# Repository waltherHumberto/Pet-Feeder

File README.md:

Este é o README para o projeto IOT de um dispensador de comida para pet, que utiliza o microcontrolador ESP32 e um servo motor para automatizar a alimentação de animais de estimação. O projeto também inclui uma configuração de aplicativo APK para controle remoto do dispensador.

Funcionalidades

    Dispensação automática de comida para animais de estimação em horários programados.
    Controle remoto do dispensador por meio de um aplicativo móvel.
    Configuração flexível de horários e quantidade de alimentação.
    Interface de usuário intuitiva para fácil operação.

Componentes do Projeto

    ESP32: Microcontrolador responsável pelo controle do dispensador e comunicação com o aplicativo móvel.
    Servo Motor: Atua como o mecanismo de dispensação da comida.
    Sensor de Alimentação: Opcionalmente, um sensor pode ser utilizado para detectar quando o recipiente de comida está vazio e enviar notificações para o aplicativo.
    Fonte de Alimentação: Fornecer energia para o ESP32, servo motor e outros componentes necessários.
    Aplicativo APK: Um aplicativo móvel que permite ao usuário controlar o dispensador remotamente, programar horários e monitorar o status de alimentação.

Instalação e Configuração

    Clone ou faça o download deste repositório para o seu computador.
    Certifique-se de ter o ambiente de desenvolvimento necessário para programar o ESP32.
    Conecte o ESP32 ao seu computador e faça o upload do código fornecido para o microcontrolador.
    Monte o servo motor no dispensador de comida, garantindo que esteja corretamente conectado ao ESP32.
    Conecte os fios do sensor de alimentação, se estiver sendo utilizado, ao ESP32.
    Conecte a fonte de alimentação ao ESP32.
    Siga as instruções fornecidas no aplicativo APK para instalá-lo em seu dispositivo móvel.
    Abra o aplicativo, siga o processo de configuração inicial para conectar o aplicativo ao ESP32.
    Configure os horários de alimentação e a quantidade de comida desejada por meio do aplicativo.

Uso

    Após configurar o dispensador e o aplicativo móvel, você pode programar horários de alimentação para o seu pet.
    O dispenser irá ativar o servo motor nos horários programados para dispensar a quantidade de comida definida.
    Você também pode usar o aplicativo para alimentar manualmente o seu pet a qualquer momento.
    O sensor de alimentação (se utilizado) irá monitorar o nível de comida no recipiente e notificará o aplicativo quando estiver vazio.

Contribuição

Contribuições são bem-vindas! Se você tiver sugestões, correções de bugs ou melhorias para este projeto, fique à vontade para enviar um pull request ou abrir uma issue neste repositório.

Licença
De Uso público

Se você tiver alguma dúvida ou precisar entrar em contato, sinta-se à vontade para enviar um e-mail para [waltherhumberto@gmail.com].

Agradecemos a todos os contribuidores e recursos de código aberto utilizados neste projeto.

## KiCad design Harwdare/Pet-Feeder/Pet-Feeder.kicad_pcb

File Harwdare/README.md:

Hardware do Dispensador de Comida para Pet

Este é o README para o hardware do projeto de Dispensador de Comida para Pet. O hardware consiste nos componentes físicos necessários para a construção e funcionamento do dispensador, incluindo o microcontrolador ESP32, o servo motor e outros elementos relevantes.
Componentes

    ESP32: Microcontrolador responsável pelo controle do dispensador e comunicação com o aplicativo móvel.
    Servo Motor: Mecanismo de dispensação da comida, utilizado para movimentar o compartimento de armazenamento.
    Sensor de Nível de Comida (opcional): Sensor utilizado para detectar o nível de comida no recipiente e enviar notificações para o aplicativo.
    Fonte de Alimentação: Fornecer energia para o ESP32, servo motor e outros componentes necessários.
    Recipiente de Comida: Compartimento onde a comida para pet é armazenada.
    Botões ou Interface de Controle: Componentes utilizados para a interação com o dispensador, como programação manual e ajuste de configurações.

Montagem

    Conecte o servo motor ao ESP32 seguindo as especificações do fabricante e as instruções do firmware.
    Conecte o sensor de nível de comida (se utilizado) ao ESP32, de acordo com as instruções da biblioteca correspondente.
    Certifique-se de que o ESP32 esteja devidamente alimentado com a fonte de alimentação adequada.
    Monte o recipiente de comida no local designado, garantindo que esteja bem fixado.
    Verifique a correta conexão e posicionamento dos botões ou da interface de controle para facilitar a interação com o dispensador.

Configuração Adicional

    Caso seja necessário, conecte o dispensador à rede Wi-Fi para permitir a comunicação com o aplicativo móvel.
    Certifique-se de configurar corretamente o firmware para que o hardware e o aplicativo móvel estejam sincronizados.

Uso

    Após a montagem e configuração do hardware, alimente o dispensador com energia.
    O microcontrolador ESP32 irá inicializar e aguardar os comandos do aplicativo móvel ou dos botões de controle.
    Utilize o aplicativo móvel para programar horários de alimentação, configurar a quantidade de comida e outras preferências.
    Quando o horário de alimentação programado for alcançado, o microcontrolador acionará o servo motor para dispensar a quantidade de comida definida.
    Caso seja utilizado um sensor de nível de comida, ele irá monitorar o recipiente e enviar notificações quando estiver vazio.
    O usuário também pode utilizar os botões ou a interface de controle para programar manualmente a alimentação ou ajustar as configurações.

Contribuição

Contribuições são bem-vindas! Se você tiver sugestões, correções ou melhorias relacionadas ao hardware do dispensador de comida para pet, fique à vontade para enviar um pull request ou abrir uma issue neste repositório.

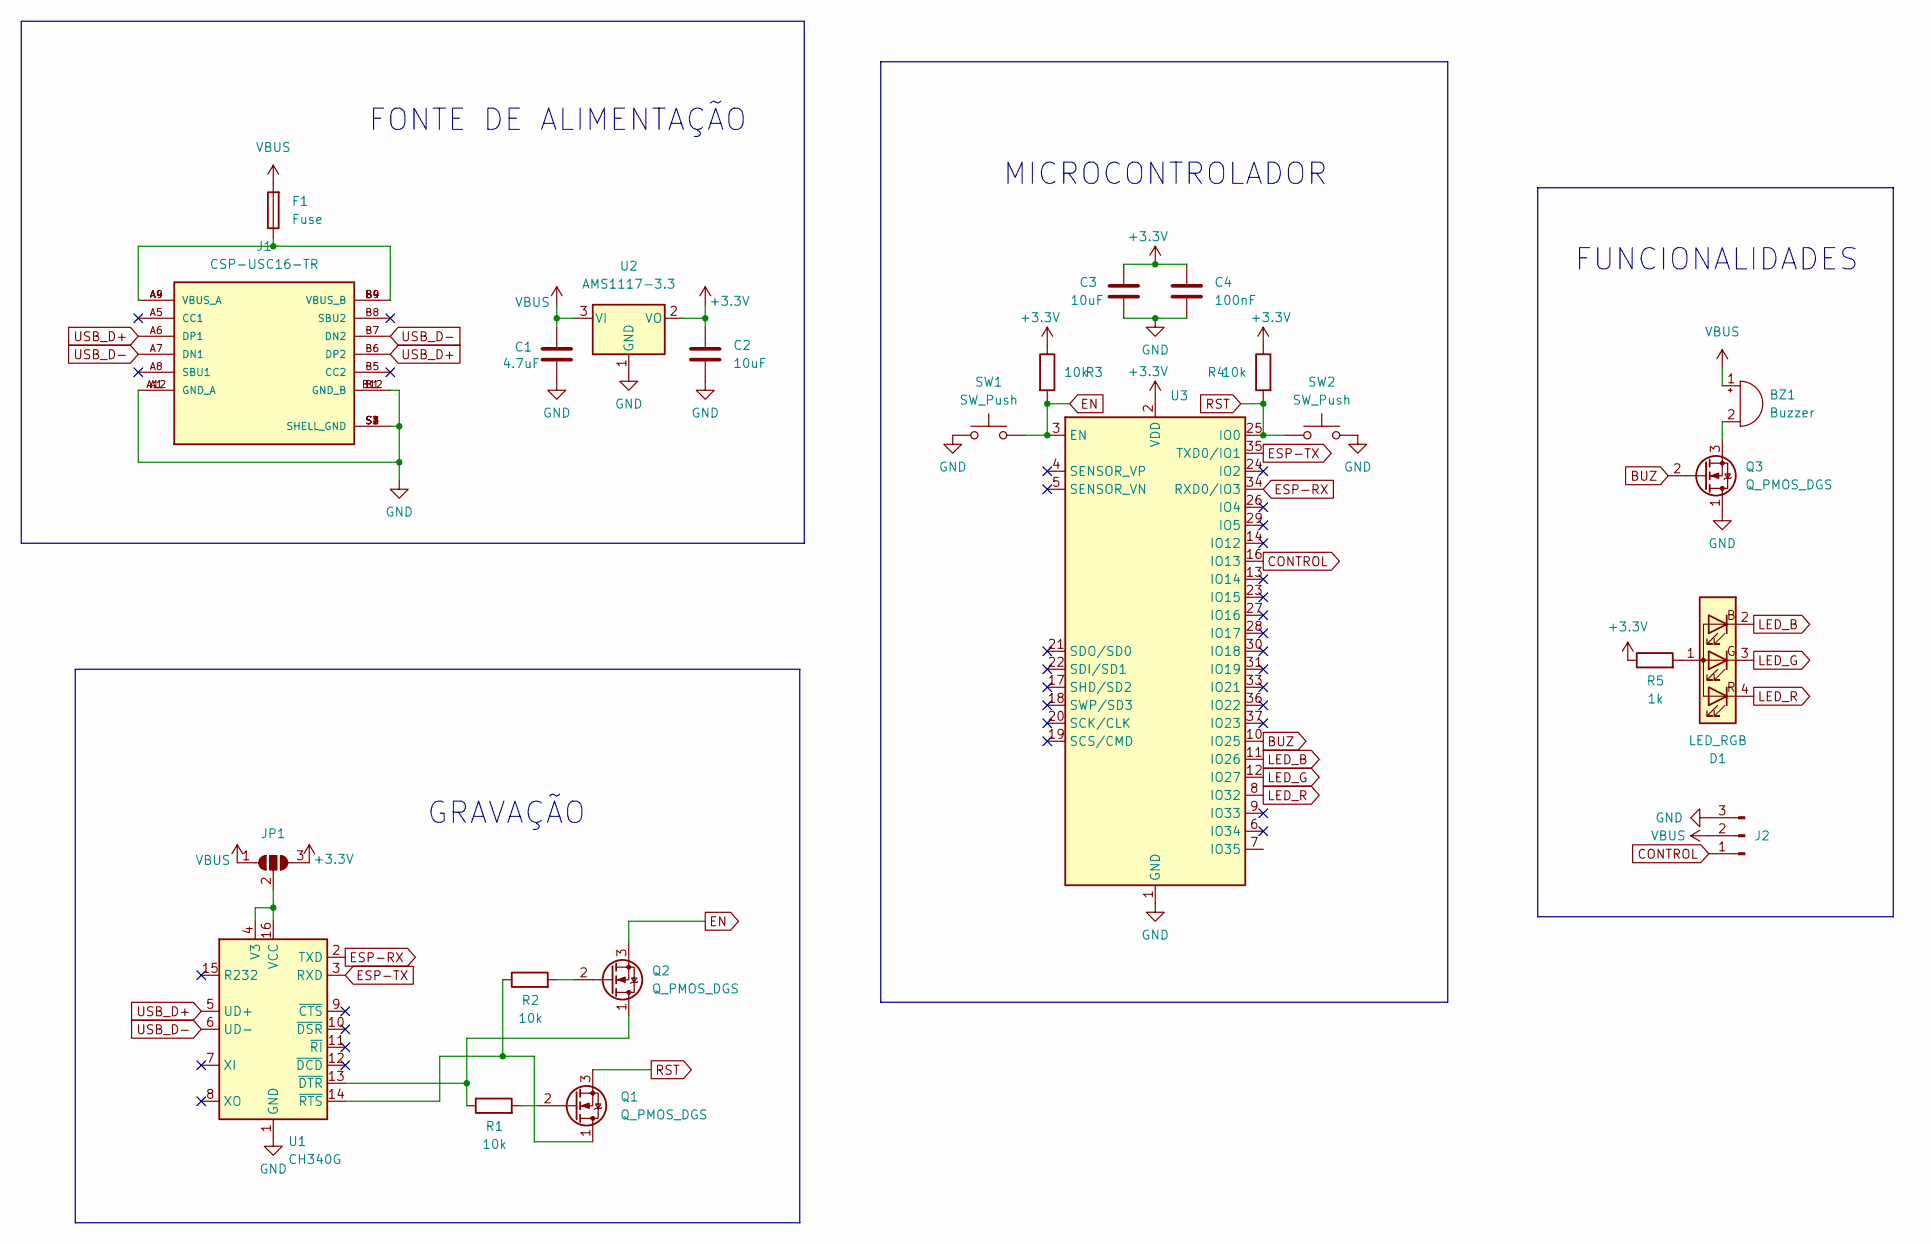
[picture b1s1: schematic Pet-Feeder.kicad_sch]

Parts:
BZ1: Buzzer; Buzzer_12x9.5RM7.6
C1: 4.7uF; C_1206_3216Metric
C2: 10uF; C_1206_3216Metric
C3: 10uF; C_0201_0603Metric
C4: 100nF; C_1206_3216Metric
D1: LED_RGB; LED_Avago_PLCC4_3.2x2.8mm_CW
F1: Fuse; R_1206_3216Metric
J1: CSP-USC16-TR; USB_C_Receptacle_Palconn_UTC16-G; PARTREV A0
J2: Conn_01x03_Male; PinSocket_1x03_P2.54mm_Vertical
JP1: SolderJumper_3_Open; SolderJumper-3_P1.3mm_Open_RoundedPad1.0x1.5mm
Q1, Q2, Q3: Q_PMOS_DGS; SOT-23-3
R1, R2, R3, R4: 10k; R_0201_0603Metric
R5: 1k; R_0201_0603Metric
SW1, SW2: SW_Push; SW_Push_1P1T_NO_CK_KSC6xxJ
U1: CH340G; SOIC-16_3.9x9.9mm_P1.27mm
U2: AMS1117-3.3; SOT-223-3_TabPin2
U3: ESP32-WROOM-32D; ESP32-WROOM-32

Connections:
+3.3V: C2.1, C3.1, C4.1, JP1.3 (B), R3.1, R4.1, R5.1, U2.2 (VO), U3.2 (VDD)
BUZ: Q3.2 (G), U3.10 (IO25)
CONTROL: J2.1, U3.16 (IO13)
EN: Q2.3 (S), R3.2, SW1.2, U3.3 (EN)
ESP-RX: U1.2 (TXD), U3.34 (RXD0/IO3)
ESP-TX: U1.3 (RXD), U3.35 (TXD0/IO1)
GND: C1.2, C2.2, C3.2, C4.2, J1.A1 (GND_A), J1.A12 (GND_A), J1.B1 (GND_B), J1.B12 (GND_B), J1.S1 (SHELL_GND), J1.S2 (SHELL_GND), J1.S3 (SHELL_GND), J1.S4 (SHELL_GND), J2.3, Q3.1 (D), SW1.1, SW2.1, U1.1 (GND), U2.1 (GND), U3.1 (GND), U3.15 (GND), U3.38 (GND), U3.39 (GND)
LED_B: D1.2 (BK), U3.11 (IO26)
LED_G: D1.3 (GK), U3.12 (IO27)
LED_R: D1.4 (RK), U3.8 (IO32)
unnamed: BZ1.2 (+), Q3.3 (S)
unnamed: D1.1 (A), R5.2
unnamed: F1.1, J1.A4 (VBUS_A), J1.A9 (VBUS_A), J1.B4 (VBUS_B), J1.B9 (VBUS_B)
unnamed: JP1.2 (C), U1.4 (V3), U1.16 (VCC)
unnamed: Q2.1 (D), R1.1, U1.13 (~DTR)
unnamed: Q1.2 (G), R1.2
unnamed: Q2.2 (G), R2.2
unnamed: Q1.1 (D), R2.1, U1.14 (~RTS)
RST: Q1.3 (S), R4.2, SW2.2, U3.25 (IO0)
USB_D+: J1.A6 (DP1), J1.B6 (DP2), U1.5 (UD+)
USB_D-: J1.A7 (DN1), J1.B7 (DN2), U1.6 (UD-)
VBUS: BZ1.1 (-), C1.1, F1.2, J2.2, JP1.1 (A), U2.3 (VI)

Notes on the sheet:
FONTE DE ALIMENTAÇÃO
MICROCONTROLADOR
GRAVAÇÃO
FUNCIONALIDADES

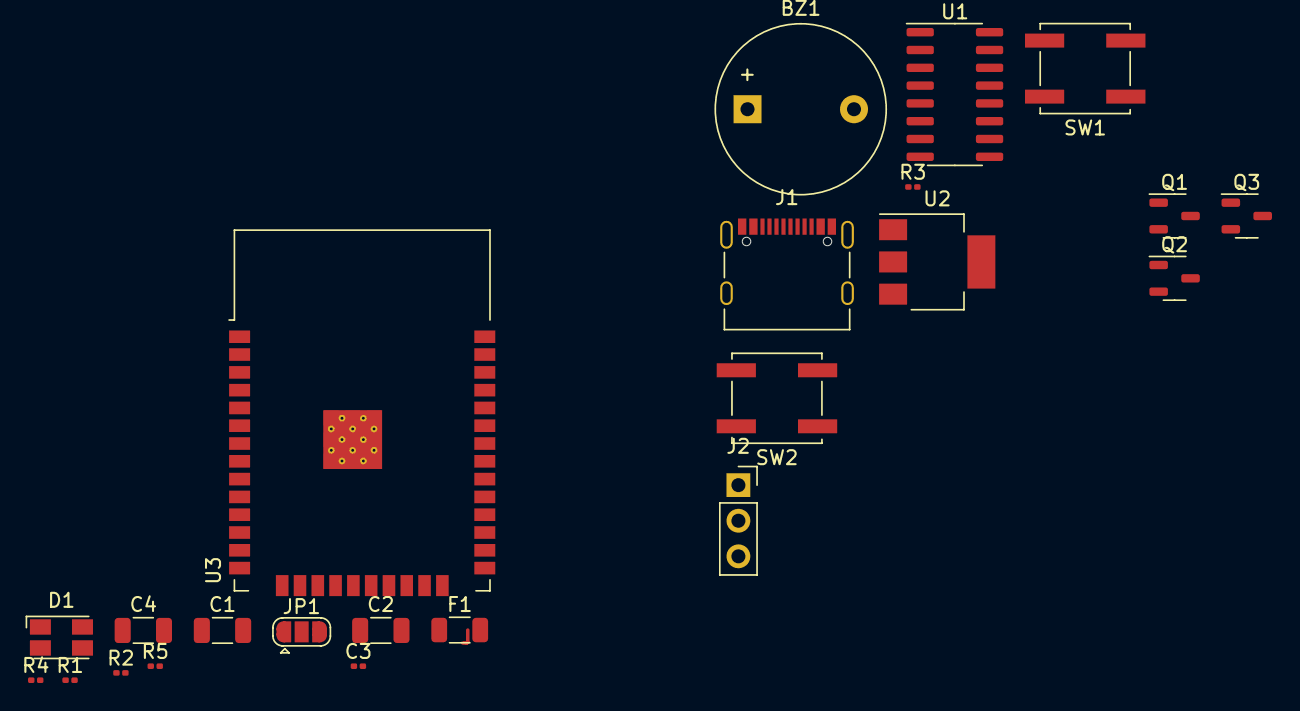
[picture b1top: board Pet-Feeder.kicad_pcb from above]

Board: 2 copper layers, 23 parts (0 on the bottom side), 22 nets.

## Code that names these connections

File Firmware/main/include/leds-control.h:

#define LED_R 32
#define LED_G 27
#define LED_B 26

void init_leds();

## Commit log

2023-07-14 Inicio do projeto
2023-07-14 Criando as pastas do projeto
2023-07-14 Mexendo no inicial do hardware
2023-07-15 Terminei o esquematico
2023-07-15 Comecei a separar como eu quero que o codigo esteja
2023-07-17 Troquei para o esp 4.4
2023-07-21 Começando a por a estrutura mqtt
2023-07-24 Mudei o algoritmo de receber mqtt
2023-08-01 Salvando para commitar
